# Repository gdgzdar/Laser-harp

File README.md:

# Laser harp
##Project in progress...

#contact:
- j.cerny.zdar@gmail.com            - organizator
- gdgzdarnadsazavou@gmail.com       - company

##Hardware:
Sensor in frame is 100% completed

Lasers in frame is 100% completed

Arduino LCD display is 1% completed

Ardduino pragraming is 30% completed

##Sofware:
Play sound functions are completed

Play sound async is  completed

Program GUI is 50% completed

Sound Librery now has 8 instruments

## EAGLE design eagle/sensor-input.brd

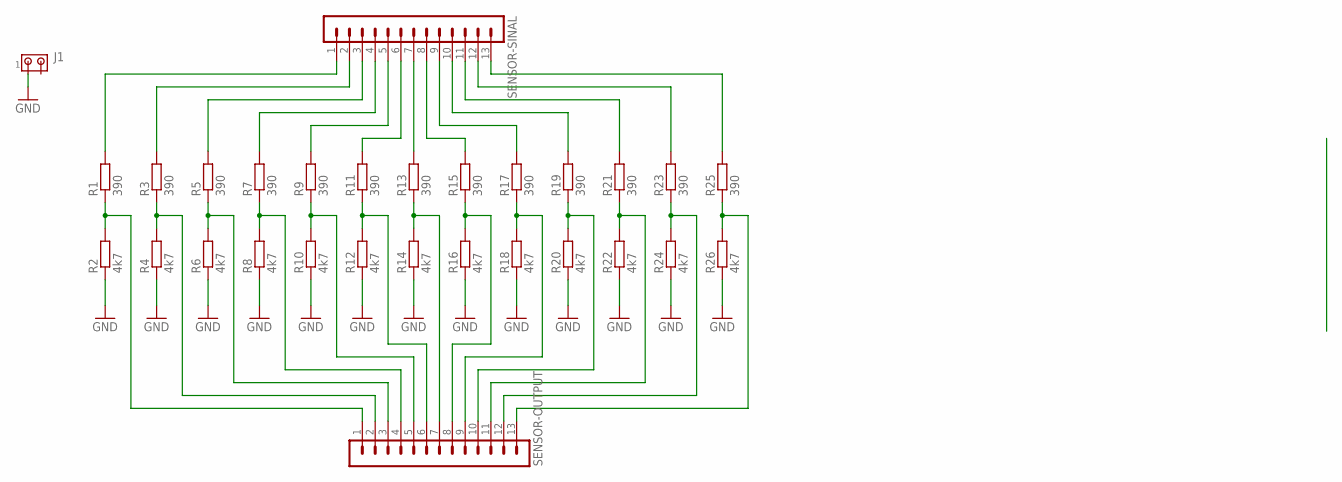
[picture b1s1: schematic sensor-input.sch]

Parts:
J1: MTA02-100; 10X02MTA
R1, R3, R5, R7, R9, R11, R13, R15, R17, R19, R21, R23, R25: 390; 0207/7
R2, R4, R6, R8, R10, R12, R14, R16, R18, R20, R22, R24, R26: 4k7; 0207/7
SENSOR-OUTPUT: MA13-1
SENSOR-SINAL: MA13-1

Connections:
GND: J1.1, R2.1, R4.1, R6.1, R8.1, R10.1, R12.1, R14.1, R16.1, R18.1, R20.1, R22.1, R24.1, R26.1
unnamed: R3.1, R4.2, SENSOR-OUTPUT.2
unnamed: R1.1, R2.2, SENSOR-OUTPUT.1
unnamed: R5.1, R6.2, SENSOR-OUTPUT.3
unnamed: R7.1, R8.2, SENSOR-OUTPUT.4
unnamed: R9.1, R10.2, SENSOR-OUTPUT.5
unnamed: R11.1, R12.2, SENSOR-OUTPUT.6
unnamed: R13.1, R14.2, SENSOR-OUTPUT.7
unnamed: R15.1, R16.2, SENSOR-OUTPUT.8
unnamed: R17.1, R18.2, SENSOR-OUTPUT.9
unnamed: R19.1, R20.2, SENSOR-OUTPUT.10
unnamed: R21.1, R22.2, SENSOR-OUTPUT.11
unnamed: R23.1, R24.2, SENSOR-OUTPUT.12
unnamed: R25.1, R26.2, SENSOR-OUTPUT.13
unnamed: R1.2, SENSOR-SINAL.1
unnamed: R3.2, SENSOR-SINAL.2
unnamed: R5.2, SENSOR-SINAL.3
unnamed: R7.2, SENSOR-SINAL.4
unnamed: R9.2, SENSOR-SINAL.5
unnamed: R11.2, SENSOR-SINAL.6
unnamed: R13.2, SENSOR-SINAL.7
unnamed: R15.2, SENSOR-SINAL.8
unnamed: R17.2, SENSOR-SINAL.9
unnamed: R19.2, SENSOR-SINAL.10
unnamed: R21.2, SENSOR-SINAL.11
unnamed: R23.2, SENSOR-SINAL.12
unnamed: R25.2, SENSOR-SINAL.13

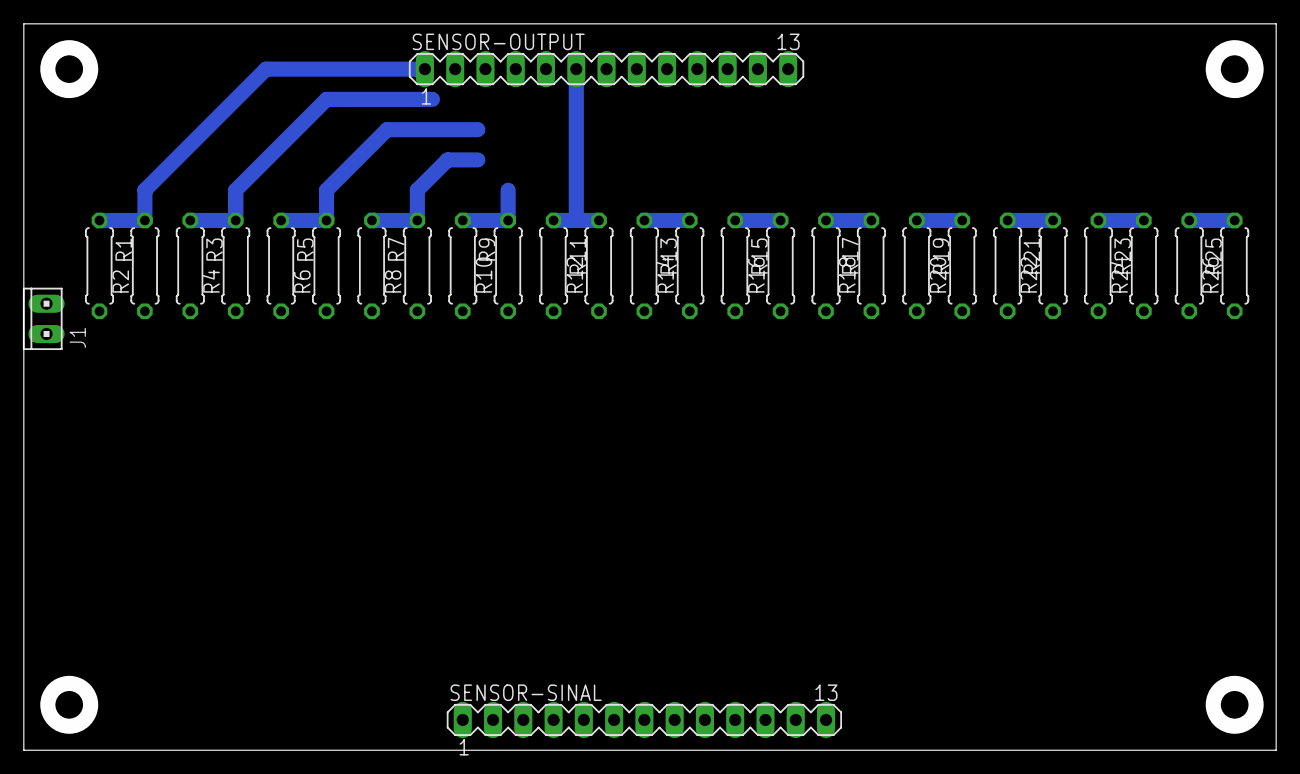
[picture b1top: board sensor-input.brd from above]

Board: 2 copper layers, 103.8 x 59.7 mm, 29 parts (0 on the bottom side), 27 nets.

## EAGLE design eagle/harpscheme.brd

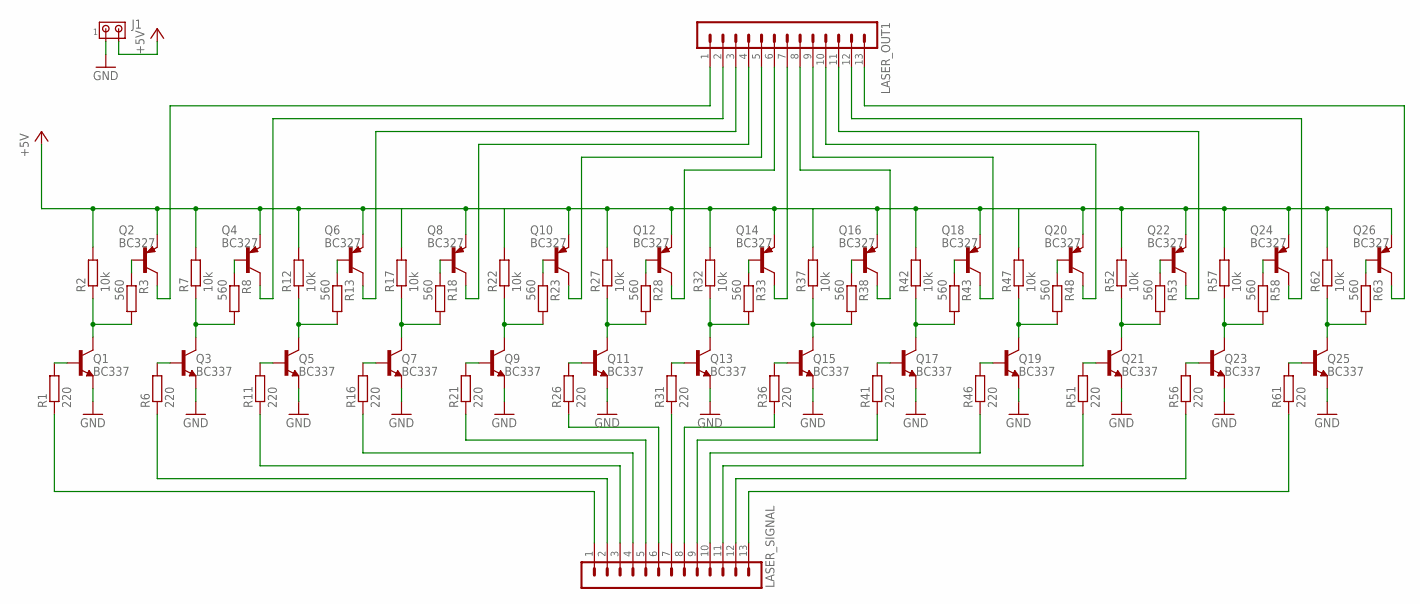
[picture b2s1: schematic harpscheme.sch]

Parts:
J1: MTA02-100; 10X02MTA
LASER_OUT1: MA13-1
LASER_SIGNAL: MA13-1
Q1, Q3, Q5, Q7, Q9, Q11, Q13, Q15, Q17, Q19, Q21, Q23, Q25: BC337; TO92
Q2, Q4, Q6, Q8, Q10, Q12, Q14, Q16, Q18, Q20, Q22, Q24, Q26: BC327; TO92-EBC
R1, R6, R11, R16, R21, R26, R31, R36, R41, R46, R51, R56, R61: 220; 0207/7
R2, R7, R12, R17, R22, R27, R32, R37, R42, R47, R52, R57, R62: 10k; 0207/7
R3, R8, R13, R18, R23, R28, R33, R38, R43, R48, R53, R58, R63: 560; 0207/7

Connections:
+5V: J1.2, Q2.E, Q4.E, Q6.E, Q8.E, Q10.E, Q12.E, Q14.E, Q16.E, Q18.E, Q20.E, Q22.E, Q24.E, Q26.E, R2.2, R7.2, R12.2, R17.2, R22.2, R27.2, R32.2, R37.2, R42.2, R47.2, R52.2, R57.2, R62.2
GND: J1.1, Q1.1 (E), Q3.1 (E), Q5.1 (E), Q7.1 (E), Q9.1 (E), Q11.1 (E), Q13.1 (E), Q15.1 (E), Q17.1 (E), Q19.1 (E), Q21.1 (E), Q23.1 (E), Q25.1 (E)
unnamed: Q1.2 (B), R1.2
unnamed: Q1.3 (C), R2.1, R3.2
unnamed: Q2.B, R3.1
unnamed: LASER_SIGNAL.7, R31.1
unnamed: LASER_OUT1.1, Q2.C
unnamed: Q3.2 (B), R6.2
unnamed: Q3.3 (C), R7.1, R8.2
unnamed: Q4.B, R8.1
unnamed: LASER_OUT1.2, Q4.C
unnamed: Q5.2 (B), R11.2
unnamed: Q5.3 (C), R12.1, R13.2
unnamed: Q6.B, R13.1
unnamed: LASER_SIGNAL.6, R26.1
unnamed: LASER_OUT1.3, Q6.C
unnamed: Q7.2 (B), R16.2
unnamed: Q7.3 (C), R17.1, R18.2
unnamed: Q8.B, R18.1
unnamed: LASER_SIGNAL.5, R21.1
unnamed: LASER_OUT1.4, Q8.C
unnamed: Q9.2 (B), R21.2
unnamed: Q9.3 (C), R22.1, R23.2
unnamed: Q10.B, R23.1
unnamed: LASER_SIGNAL.4, R16.1
unnamed: LASER_OUT1.5, Q10.C
unnamed: Q11.2 (B), R26.2
unnamed: Q11.3 (C), R27.1, R28.2
unnamed: Q12.B, R28.1
unnamed: LASER_SIGNAL.3, R11.1
unnamed: LASER_OUT1.6, Q12.C
unnamed: Q13.2 (B), R31.2
unnamed: Q13.3 (C), R32.1, R33.2
unnamed: Q14.B, R33.1
unnamed: LASER_SIGNAL.2, R6.1
unnamed: LASER_OUT1.7, Q14.C
unnamed: Q15.2 (B), R36.2
unnamed: Q15.3 (C), R37.1, R38.2
unnamed: Q16.B, R38.1
unnamed: LASER_SIGNAL.1, R1.1
unnamed: LASER_OUT1.8, Q16.C
unnamed: Q17.2 (B), R41.2
unnamed: Q17.3 (C), R42.1, R43.2
unnamed: Q18.B, R43.1
unnamed: LASER_SIGNAL.8, R36.1
unnamed: LASER_OUT1.9, Q18.C
unnamed: Q19.2 (B), R46.2
unnamed: Q19.3 (C), R47.1, R48.2
unnamed: Q20.B, R48.1
unnamed: LASER_SIGNAL.9, R41.1
unnamed: LASER_OUT1.10, Q20.C
unnamed: Q21.2 (B), R51.2
unnamed: Q21.3 (C), R52.1, R53.2
unnamed: Q22.B, R53.1
unnamed: LASER_SIGNAL.10, R46.1
unnamed: LASER_OUT1.11, Q22.C
unnamed: Q23.2 (B), R56.2
unnamed: Q23.3 (C), R57.1, R58.2
unnamed: Q24.B, R58.1
unnamed: LASER_SIGNAL.11, R51.1
unnamed: LASER_OUT1.12, Q24.C
unnamed: Q25.2 (B), R61.2
unnamed: Q25.3 (C), R62.1, R63.2
unnamed: Q26.B, R63.1
unnamed: LASER_SIGNAL.12, R56.1
unnamed: LASER_OUT1.13, Q26.C
unnamed: LASER_SIGNAL.13, R61.1

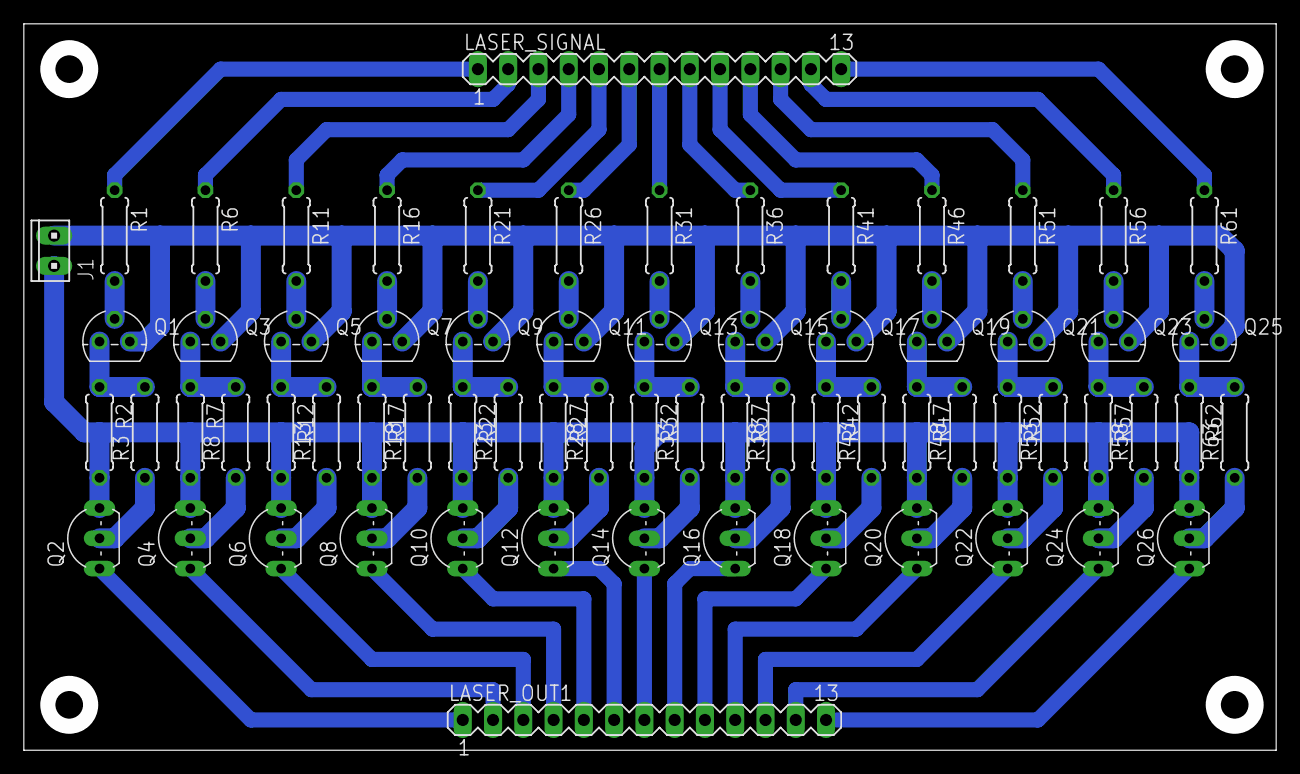
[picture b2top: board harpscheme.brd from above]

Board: 2 copper layers, 103.8 x 59.7 mm, 68 parts (0 on the bottom side), 67 nets.

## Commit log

2015-09-25 add license.txt
2015-10-23 add sound library
2015-10-23 Add reading inputs
2015-11-15 add sounds without quiet
2015-11-15 add playing sounds with a choice of musical instrument
2015-11-15 add .pyc files to .gitignore
2016-01-28 Add serial print
2016-02-11 create gui with menu and logo
2016-02-18 add code to class Harp
2016-03-30 add code for reading from serial
2016-04-07 Refactor Arduino SW
2016-05-20 add method for rendering notes
2016-05-20 add images of notes
2016-05-20 add images for bass notes
2016-05-20 add method for playing sounds from keyboard
2016-05-21 add images of musical instruments
2016-05-21 refactor directory names for arduino firmware
2016-05-21 make harp firmware object-oriented
2016-05-21 add laser harp simulator - virtual harp
2016-05-21 remove duplicite sound data
2016-05-22 add scale widget for changing volume with support for Ubuntu
2016-05-24 fix compatibility issues with tkinter and openal
2016-05-27 remove temporary file Part_list which contained neccessary HW components
2016-05-27 add files with dependencies
2016-05-27 remove unused library
2016-05-27 add design to dialog window
2016-05-27 refactor firmware directry structure
2016-05-27 add Joystick controller to firmware
2016-06-03 simplify virtual-harp.ino
2016-06-03 refactor harp-communicator firmware
2016-06-03 refactor joystick.cpp
2016-06-10 fix critical issue
2016-06-10 create responsible UI
2016-06-10 refactor and fix joystick read error
2016-06-10 change orientation of joystick
2016-06-10 add dependencies
2016-06-17 Add some sounds and harp interface classes
2016-06-19 add method for reading from serial port from arduino
2016-06-25 create gh-pages, initial commit
2016-06-25 add harp illustration
2016-06-25 design unification
2016-06-25 create content structure
2016-06-25 add progress gallery template
2016-06-25 improve progress gallery, add video template
2016-06-25 add team profiles template
2016-06-27 design improvement, css files merge
2016-06-27 few minor style improvement
2016-06-27 add sample-code section template
2016-06-27 color redesign
2016-06-27 add method to GUI for reading from Arduino
2016-08-13 repair sounds
2016-09-23 Add team profile pictures
2016-09-23 Add team members links
2016-11-25 add pygame player for asynchronously playing sound
2017-01-10 add reader component
2017-01-18 add audio component
2017-01-20 add thread for player which is listening to arduino and printing what ardiuno sends
2017-01-20 add playing notes from arduino
2017-01-22 update dependecies
2017-02-03 add method for getting list of available ports
2017-02-03 move function for getting available ports to class Reader
2017-02-03 Add StartUp dialog
2017-02-03 Add Milan Lempera to the team section
2017-02-03 Fix SVG text
2017-02-03 Add first part of about text (draft)
2017-02-03 Add two pictures (box and completed harp) of progress
2017-02-03 add eagle schema & board
2017-02-03 add vk file and edit git ingore
2017-02-15 eagle - board draft
2017-03-10 add menu template without colors
2017-03-10 add colors to left side menu
2017-03-10 add image
2017-03-24 add logo image
2017-03-24 add empty stave
2017-04-01 add sensor input schema
2017-05-12 add rerendering stave on note played
